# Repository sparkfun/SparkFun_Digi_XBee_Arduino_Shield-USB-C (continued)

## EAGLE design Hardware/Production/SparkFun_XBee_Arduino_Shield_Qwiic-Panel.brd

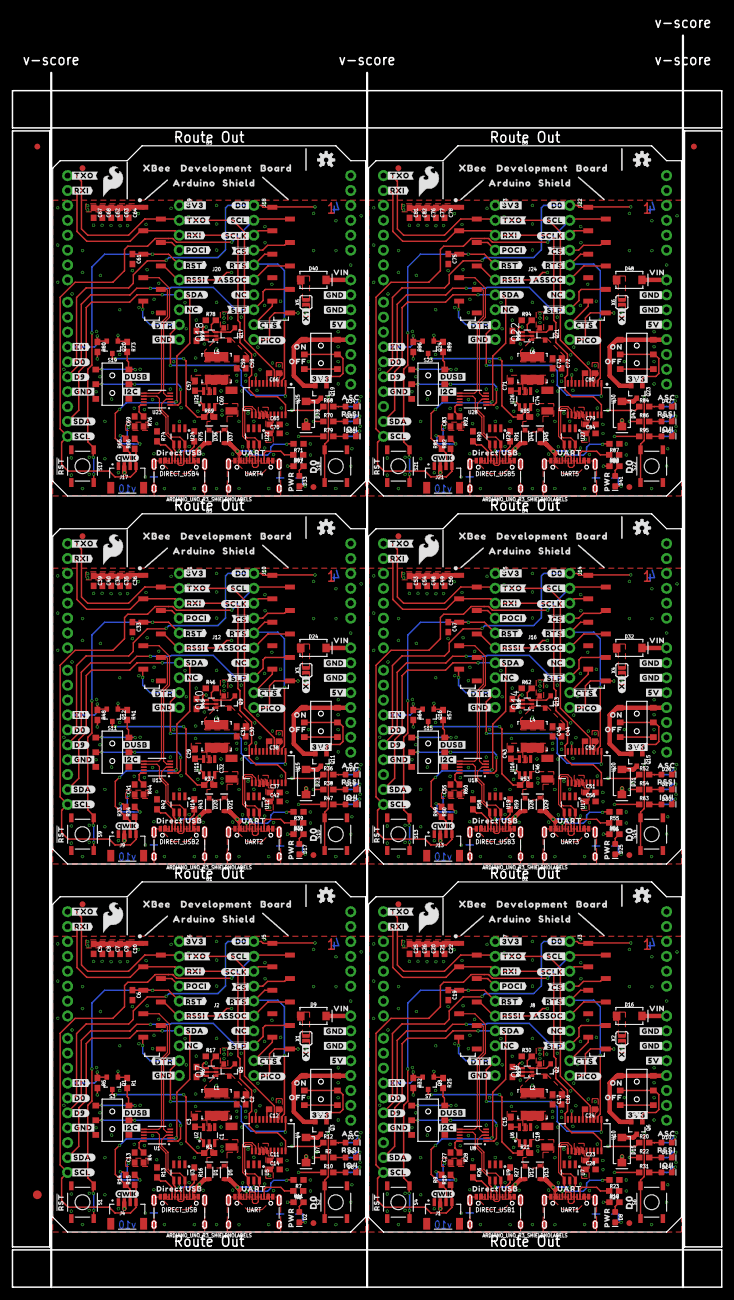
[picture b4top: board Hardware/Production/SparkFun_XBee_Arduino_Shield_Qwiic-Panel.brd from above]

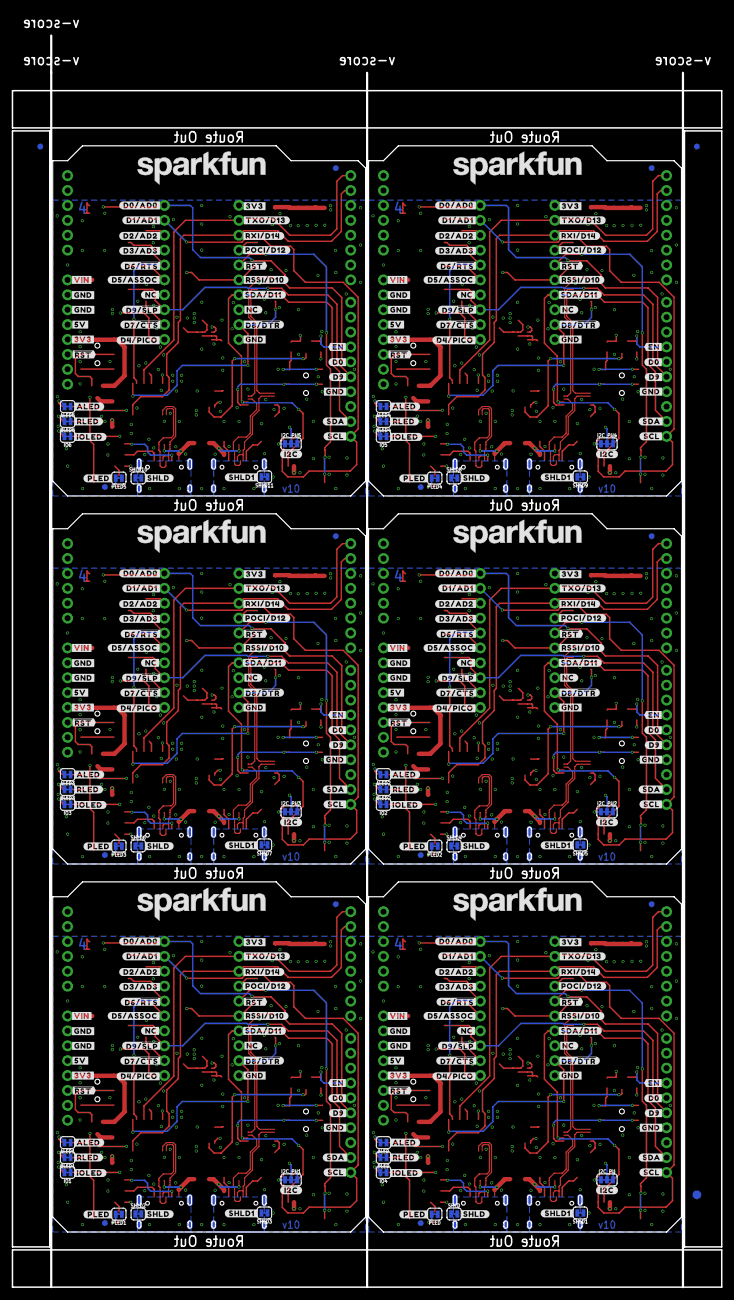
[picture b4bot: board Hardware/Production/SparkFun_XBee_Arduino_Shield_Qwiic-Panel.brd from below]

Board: 4 copper layers, 120.8 x 217.2 mm, 1008 parts (297 on the bottom side), 348 nets.

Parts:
ALED, ALED1, ALED2, ALED3, ALED4, ALED5: JUMPER-SMT_2_NC_TRACE_SILK; SMT-JUMPER_2_NC_TRACE_SILK
B1, B2, B3, B4, B5, B6: ARDUINO_UNO_R3_SHIELDNOLABELS; UNO_R3_SHIELD_NOLABELS
C1, C18, C32, C46, C60, C74: 10uF; 1210
C2, C4, C16, C17, C30, C31, C44, C45, C58, C59, C72, C73: 22uF; 0603
C3, C9, C11, C12, C13, C15, C21, C23, C24, C27, C29, C35, C37, C38, C41, C43, C49, C51, C52, C55, C57, C63, C65, C66, C69, C71, C77, C79, C80, C83: 0.1uF; 0603
C5, C25, C39, C53, C67, C81: 47pF; 0603
C6, C7, C19, C20, C33, C34, C47, C48, C61, C62, C75, C76: 10nF; 0603
C8, C26, C40, C54, C68, C82: 10pF; 0603
C10, C22, C36, C50, C64, C78: 10uF; 0603
C14, C28, C42, C56, C70, C84: 4.7uF; 0603
D1, D5, D12, D13, D20, D21, D28, D29, D36, D37, D44, D45: 3A/10V/280mV; SOD-323
D2, D8, D17, D25, D33, D41: RED; LED-0603
D3, D10, D18, D26, D34, D42: BLUE; LED-0603
D4, D11, D19, D27, D35, D43: Yellow; LED-0603
D6, D14, D22, D30, D38, D46: GREEN; LED-0603
D7, D9, D15, D16, D23, D24, D31, D32, D39, D40, D47, D48: 3A/40V/500mV; SMA-DIODE
DIRECT_USB, DIRECT_USB1, DIRECT_USB2, DIRECT_USB3, DIRECT_USB4, DIRECT_USB5: USB Female Type C Connector; USB-C-16P-4LAYER-ISOLATED
E$1, E$2, E$3, E$4: FIDUCIAL-1X2
E$5, E$6: FIDUCIAL-1.5X3
FD1, FD2, FD3, FD4, FD5, FD6, FD7, FD8, FD9, FD10, FD11, FD12, FD13, FD14, FD15, FD16, FD17, FD18, FD19, FD20, FD21, FD22, FD23, FD24: FIDUCIAL1X2; FIDUCIAL-1X2
I2C_PU, I2C_PU1, I2C_PU2, I2C_PU3, I2C_PU4, I2C_PU5: JUMPER-SMT_3_2-NC_TRACE_SILK; SMT-JUMPER_3_2-NC_TRACE_SILK
IO1, IO2, IO3, IO4, IO5, IO6: JUMPER-SMT_2_NC_TRACE_SILK; SMT-JUMPER_2_NC_TRACE_SILK
J1, J4, J9, J13, J17, J21: QWIIC_RIGHT_ANGLE; JST04_1MM_RA
J2, J8, J12, J16, J20, J24: XBEE3-SMD
J3, J5, J6, J7, J10, J11, J14, J15, J18, J19, J22, J23: 1X10_NO_SILK
L1, L2, L3, L4, L5, L6: 3.9UH; INDUCTOR_3.9UH
LOGO1, LOGO7, LOGO11, LOGO15, LOGO19, LOGO23: SFE_LOGO_NAMEBLANK; BLANK
LOGO2, LOGO5, LOGO9, LOGO13, LOGO17, LOGO21: OSHW-LOGOS; OSHW-LOGO-S
LOGO3, LOGO6, LOGO10, LOGO14, LOGO18, LOGO22: QWIIC_LOGO_4MM; QWIIC_4MM
LOGO4, LOGO8, LOGO12, LOGO16, LOGO20, LOGO24: SPECIAL_INSTRUCTIONS-ORDERING; ORDERING_INSTRUCTIONS
PLED, PLED1, PLED2, PLED3, PLED4, PLED5: JUMPER-SMT_2_NC_TRACE_SILK; SMT-JUMPER_2_NC_TRACE_SILK
Q1, Q8, Q12, Q16, Q20, Q24: 220mA/50V/3.5Ω; SOT23-3
Q2, Q5, Q9, Q13, Q17, Q21: 20V/4.2A/52mΩ/1.4W; SOT23-3
Q3, Q6, Q11, Q15, Q19, Q23: 3.1A/30V/105mΩ; SOT23-3
Q4, Q7, Q10, Q14, Q18, Q22: SOT363_PHILIPS
R1, R3, R6, R21, R25, R29, R37, R41, R45, R53, R57, R61, R69, R73, R77, R85, R89, R93: 100k; 0603
R2, R9, R12, R14, R15, R18, R20, R22, R33, R34, R36, R38, R49, R50, R52, R54, R65, R66, R68, R70, R81, R82, R84, R86: 2.2k; 0603
R4, R28, R44, R60, R76, R92: 100; 0603
R5, R32, R48, R64, R80, R96: 10k; 0603
R7, R8, R13, R16, R23, R24, R26, R27, R39, R40, R42, R43, R55, R56, R58, R59, R71, R72, R74, R75, R87, R88, R90, R91: 5.1k; 0603
R10, R31, R47, R63, R79, R95: 330; 0603
R11, R19, R35, R51, R67, R83: 4.7k; 0603
R17, R30, R46, R62, R78, R94: 1M; 0603
RLED, RLED1, RLED2, RLED3, RLED4, RLED5: JUMPER-SMT_2_NC_TRACE_SILK; SMT-JUMPER_2_NC_TRACE_SILK
S1, S2, S4, S6, S9, S10, S13, S14, S17, S18, S21, S22: TACTILE_SWITCH_SMD_5.2MM
S3, S5, S7, S8, S11, S12, S15, S16, S19, S20, S23, S24: SWITCH_DPDT_SMD_AYZ0202
SHLD, SHLD1, SHLD2, SHLD3, SHLD4, SHLD5, SHLD6, SHLD7, SHLD8, SHLD9, SHLD10, SHLD11: JUMPER-SMT_2_NC_TRACE_SILK; SMT-JUMPER_2_NC_TRACE_SILK
U1, U8, U13, U18, U23, U28: FSUSB30MUX_MSOP10; MSOP10
U2, U6, U11, U16, U21, U26: AP63203; SOT23-6
U3, U5, U7, U9, U12, U14, U17, U19, U22, U24, U27, U29: ESD Diode; SOT-23-6
U4, U10, U15, U20, U25, U30: FT231XS; SSOP20_L
U$1, U$146, U$238, U$330, U$422, U$514: RSSI31
U$2, U$147, U$239, U$331, U$423, U$515: PWR29
U$3, U$56, U$120, U$134, U$212, U$226, U$304, U$318, U$396, U$410, U$488, U$502: #SDA#10
U$4, U$127, U$219, U$311, U$403, U$495: #SHLD#36
U$5, U$9, U$128, U$133, U$220, U$225, U$312, U$317, U$404, U$409, U$496, U$501: #NC#1
U$6, U$99, U$191, U$283, U$375, U$467: #D3#AD3#23
U$7, U$10, U$129, U$130, U$221, U$222, U$313, U$314, U$405, U$406, U$497, U$498: #NC#3
U$8, U$159, U$251, U$343, U$435, U$527: ##DTR##27
U$11, U$97, U$189, U$281, U$373, U$465: #D1#AD1#8
U$12, U$160, U$252, U$344, U$436, U$528: ##CTS##28
U$13, U$105, U$197, U$289, U$381, U$473: #D8##DTR##27
U$14, U$106, U$198, U$290, U$382, U$474: #RSSI#D10#17
U$15, U$107, U$199, U$291, U$383, U$475: #SDA#D11#9
U$16, U$108, U$200, U$292, U$384, U$476: ##RST##15
U$17, U$109, U$201, U$293, U$385, U$477: #POCI#D12#24
U$18, U$110, U$202, U$294, U$386, U$478: #RXI#D14#15
U$19, U$98, U$190, U$282, U$374, U$466: #D2#AD2#19
U$20, U$100, U$192, U$284, U$376, U$468: #D6##RTS##25
U$21, U$32, U$115, U$137, U$207, U$229, U$299, U$321, U$391, U$413, U$483, U$505: #TXO#8
U$22, U$111, U$203, U$295, U$387, U$479: #TXO#D13#13
U$23, U$167, U$259, U$351, U$443, U$535: VIN5
U$24, U$135, U$227, U$319, U$411, U$503: #SCL#7
U$25, U$29, U$41, U$50, U$53, U$63, U$76, U$82, U$132, U$136, U$140, U$149, U$161, U$173, U$174, U$178, U$224, U$228, U$232, U$241, U$253, U$265, U$266, U$270, U$316, U$320, U$324, U$333, U$345, U$357, U$358, U$362, U$408, U$412, U$416, U$425, U$437, U$449, U$450, U$454, U$500, U$504, U$508, U$517, U$529, U$541, U$542, U$546: #GND#0
U$26, U$91, U$185, U$277, U$369, U$461: #I2C#33
U$27, U$33, U$116, U$138, U$208, U$230, U$300, U$322, U$392, U$414, U$484, U$506: #RXI#7
U$28, U$131, U$223, U$315, U$407, U$499: UART34
U$30, U$95, U$187, U$279, U$371, U$463: #RST#30
U$31, U$168, U$260, U$352, U$444, U$536: #PICO#27
U$34, U$169, U$261, U$353, U$445, U$537: #D9#6
U$35, U$101, U$193, U$285, U$377, U$469: #D5#ASSOC#25
U$36, U$102, U$194, U$286, U$378, U$470: #D9##SLP##28
U$37, U$103, U$195, U$287, U$379, U$471: #D7##CTS##26
U$38, U$104, U$196, U$288, U$380, U$472: #D4#PICO#25
U$39, U$66, U$155, U$175, U$247, U$267, U$339, U$359, U$431, U$451, U$523, U$543: #5V#5
U$40, U$92, U$186, U$278, U$370, U$462: D03
U$42, U$65, U$126, U$170, U$218, U$262, U$310, U$354, U$402, U$446, U$494, U$538: #D0#3
U$43, U$171, U$263, U$355, U$447, U$539: #X1#10
U$44, U$47, U$77, U$84, U$139, U$150, U$162, U$180, U$231, U$242, U$254, U$272, U$323, U$334, U$346, U$364, U$415, U$426, U$438, U$456, U$507, U$518, U$530, U$548: #3V3#1
U$45, U$117, U$209, U$301, U$393, U$485: #POCI#32
U$46, U$172, U$264, U$356, U$448, U$540: ON38
U$48, U$112, U$204, U$296, U$388, U$480: #EN#17
U$49, U$113, U$205, U$297, U$389, U$481: #ALED#21
U$51, U$114, U$206, U$298, U$390, U$482: #RLED#22
U$52, U$164, U$256, U$348, U$440, U$532: #PLED#20
U$54, U$87, U$118, U$181, U$210, U$273, U$302, U$365, U$394, U$457, U$486, U$549: ##RST##13
U$55, U$119, U$211, U$303, U$395, U$487: #RSSI#16
U$57, U$121, U$213, U$305, U$397, U$489: #ASSOC#28
U$58, U$122, U$214, U$306, U$398, U$490: ##RTS##14
U$59, U$123, U$215, U$307, U$399, U$491: ##CS##26
U$60, U$124, U$216, U$308, U$400, U$492: #SCLK#33
U$61, U$96, U$188, U$280, U$372, U$464: SFE_LOGO_FLAME_.2
U$62, U$141, U$233, U$325, U$417, U$509: SFE_LOGO_NAME_.2
U$64, U$125, U$217, U$309, U$401, U$493: #SCL#9
U$67, U$176, U$268, U$360, U$452, U$544: #SDA#9
U$68, U$142, U$234, U$326, U$418, U$510: ##SLP##28
U$69, U$163, U$255, U$347, U$439, U$531: OFF311
U$70, U$177, U$269, U$361, U$453, U$545: #SCL#13
U$71, U$143, U$235, U$327, U$419, U$511: DIRECT_USB33
U$72, U$144, U$236, U$328, U$420, U$512: #DUSB#31
U$73, U$158, U$250, U$342, U$434, U$526: #I2C#13751
U$74, U$145, U$237, U$329, U$421, U$513: ASC32
U$75, U$148, U$240, U$332, U$424, U$516: #SHLD1#37
U$78, U$151, U$243, U$335, U$427, U$519: #D0#AD0#18
U$79, U$152, U$244, U$336, U$428, U$520: ARDUINO1345
U$80, U$153, U$245, U$337, U$429, U$521: XBEE340
U$81, U$154, U$246, U$338, U$430, U$522: SHIELD1346
U$83, U$179, U$271, U$363, U$455, U$547: #EN#15
U$85, U$156, U$248, U$340, U$432, U$524: DEVELOPMENT1346
U$86, U$157, U$249, U$341, U$433, U$525: BOARD1347
U$88, U$182, U$274, U$366, U$458, U$550: #VIN#4
U$89, U$183, U$275, U$367, U$459, U$551: #D0#3416
U$90, U$184, U$276, U$368, U$460, U$552: #D9#3416
U$93, U$165, U$257, U$349, U$441, U$533: #IOLED#5
U$94, U$166, U$258, U$350, U$442, U$534: IO49
UART, UART1, UART2, UART3, UART4, UART5: USB Female Type C Connector; USB-C-16P-4LAYER-ISOLATED
X1, X2, X3, X4, X5, X6: JUMPER-SMT_2_NO_SILK; SMT-JUMPER_2_NO_SILK

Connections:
3.3V: C5.1, C7.1, C8.1, C9.1, C10.1, C11.1, C12.1, C13.1, C14.1, D7.C, I2C_PU.2, J2.1, J4.2, J6.1, Q1.1, Q5.2, Q7.4, R1.1, R4.2, R5.2, R11.1, U4.3, U4.13, U4.14, U4.15
3.3V1: C20.1, C21.1, C22.1, C23.1, C24.1, C25.1, C26.1, C27.1, C28.1, D15.C, I2C_PU1.2, J1.2, J7.1, J8.1, Q2.2, Q4.4, Q8.1, R19.1, R25.1, R28.2, R32.2, U10.3, U10.13, U10.14, U10.15
3.3V2: C34.1, C35.1, C36.1, C37.1, C38.1, C39.1, C40.1, C41.1, C42.1, D23.C, I2C_PU2.2, J9.2, J11.1, J12.1, Q9.2, Q10.4, Q12.1, R35.1, R41.1, R44.2, R48.2, U15.3, U15.13, U15.14, U15.15
3.3V3: C48.1, C49.1, C50.1, C51.1, C52.1, C53.1, C54.1, C55.1, C56.1, D31.C, I2C_PU3.2, J13.2, J15.1, J16.1, Q13.2, Q14.4, Q16.1, R51.1, R57.1, R60.2, R64.2, U20.3, U20.13, U20.14, U20.15
3.3V4: C62.1, C63.1, C64.1, C65.1, C66.1, C67.1, C68.1, C69.1, C70.1, D39.C, I2C_PU4.2, J17.2, J19.1, J20.1, Q17.2, Q18.4, Q20.1, R67.1, R73.1, R76.2, R80.2, U25.3, U25.13, U25.14, U25.15
3.3V5: C76.1, C77.1, C78.1, C79.1, C80.1, C81.1, C82.1, C83.1, C84.1, D47.C, I2C_PU5.2, J21.2, J23.1, J24.1, Q21.2, Q22.4, Q24.1, R83.1, R89.1, R92.2, R96.2, U30.3, U30.13, U30.14, U30.15
3.3V_SW: B1.3.3V, Q3.2, S5.3, S5.6
3.3V_SW1: B2.3.3V, Q6.2, S8.3, S8.6
3.3V_SW2: B3.3.3V, Q11.2, S12.3, S12.6
3.3V_SW3: B4.3.3V, Q15.2, S16.3, S16.6
3.3V_SW4: B5.3.3V, Q19.2, S20.3, S20.6
3.3V_SW5: B6.3.3V, Q23.2, S24.3, S24.6
3.3V_VREG: C2.1, C4.1, L1.P$2, Q5.3, Q7.1, U2.1
3.3V_VREG1: C16.1, C17.1, L2.P$2, Q2.3, Q4.1, U6.1
3.3V_VREG2: C30.1, C31.1, L3.P$2, Q9.3, Q10.1, U11.1
3.3V_VREG3: C44.1, C45.1, L4.P$2, Q13.3, Q14.1, U16.1
3.3V_VREG4: C58.1, C59.1, L5.P$2, Q17.3, Q18.1, U21.1
3.3V_VREG5: C72.1, C73.1, L6.P$2, Q21.3, Q22.1, U26.1
!RESET!: C6.1, J2.5, J6.5, S1.1, S1.2
!RESET!1: C19.1, J7.5, J8.5, S4.1, S4.2
!RESET!2: C33.1, J11.5, J12.5, S9.1, S9.2
!RESET!3: C47.1, J15.5, J16.5, S13.1, S13.2
!RESET!4: C61.1, J19.5, J20.5, S17.1, S17.2
!RESET!5: C75.1, J23.5, J24.5, S21.1, S21.2
D0: B1.D12, J2.20, J5.1, S2.1, S2.2
D1: B2.D12, J3.1, J8.20, S6.1, S6.2
D1/SCL: B1.SCL, J2.19, J4.4, J5.2, R15.1
D1/SCL1: B2.SCL, J1.4, J3.2, J8.19, R18.1
D1/SCL2: B3.SCL, J9.4, J10.2, J12.19, R34.1
D1/SCL3: B4.SCL, J13.4, J14.2, J16.19, R50.1
D1/SCL4: B5.SCL, J17.4, J18.2, J20.19, R66.1
D1/SCL5: B6.SCL, J21.4, J22.2, J24.19, R82.1
D2: B3.D12, J10.1, J12.20, S10.1, S10.2
D2/SPI_CLK: J2.18, J5.3
D2/SPI_CLK1: J3.3, J8.18
D2/SPI_CLK2: J10.3, J12.18
D2/SPI_CLK3: J14.3, J16.18
D2/SPI_CLK4: J18.3, J20.18
D2/SPI_CLK5: J22.3, J24.18
D3: B4.D12, J14.1, J16.20, S14.1, S14.2
D3/SPI_!CS!: J2.17, J5.4
D3/SPI_!CS!1: J3.4, J8.17
D3/SPI_!CS!2: J10.4, J12.17
D3/SPI_!CS!3: J14.4, J16.17
D3/SPI_!CS!4: J18.4, J20.17
D3/SPI_!CS!5: J22.4, J24.17
D4: B5.D12, J18.1, J20.20, S18.1, S18.2
D4/SPI_PICO: J2.11, J5.10, R10.1
D4/SPI_PICO1: J3.10, J8.11, R31.1
D4/SPI_PICO2: J10.10, J12.11, R47.1
D4/SPI_PICO3: J14.10, J16.11, R63.1
D4/SPI_PICO4: J18.10, J20.11, R79.1
D4/SPI_PICO5: J22.10, J24.11, R95.1
D5: B6.D12, J22.1, J24.20, S22.1, S22.2
D5/ASSOCIATE: J2.15, J5.6, R12.1
D5/ASSOCIATE1: J3.6, J8.15, R20.1
D5/ASSOCIATE2: J10.6, J12.15, R36.1
D5/ASSOCIATE3: J14.6, J16.15, R52.1
D5/ASSOCIATE4: J18.6, J20.15, R68.1
D5/ASSOCIATE5: J22.6, J24.15, R84.1
D6/!RTS!: J2.16, J5.5, U4.2
D6/!RTS!1: J3.5, J8.16, U10.2
D6/!RTS!2: J10.5, J12.16, U15.2
D6/!RTS!3: J14.5, J16.16, U20.2
D6/!RTS!4: J18.5, J20.16, U25.2
D6/!RTS!5: J22.5, J24.16, U30.2
D7/!CTS!: J2.12, J5.9, U4.9
D7/!CTS!1: J3.9, J8.12, U10.9
D7/!CTS!2: J10.9, J12.12, U15.9
D7/!CTS!3: J14.9, J16.12, U20.9
D7/!CTS!4: J18.9, J20.12, U25.9
D7/!CTS!5: J22.9, J24.12, U30.9
D8/!DTR!: J2.9, J6.9, U4.1
D8/!DTR!1: J7.9, J8.9, U10.1
D8/!DTR!2: J11.9, J12.9, U15.1
D8/!DTR!3: J15.9, J16.9, U20.1
D8/!DTR!4: J19.9, J20.9, U25.1
D8/!DTR!5: J23.9, J24.9, U30.1
D9/!SLEEP!: B1.D13, J2.13, J5.8
D9/!SLEEP!1: B2.D13, J3.8, J8.13
D9/!SLEEP!2: B3.D13, J10.8, J12.13
D9/!SLEEP!3: B4.D13, J14.8, J16.13
D9/!SLEEP!4: B5.D13, J18.8, J20.13
D9/!SLEEP!5: B6.D13, J22.8, J24.13
D10/RSSI_PWM: J2.6, J6.6, R2.1
D10/RSSI_PWM1: J7.6, J8.6, R22.1
D10/RSSI_PWM2: J11.6, J12.6, R38.1
D10/RSSI_PWM3: J15.6, J16.6, R54.1
D10/RSSI_PWM4: J19.6, J20.6, R70.1
D10/RSSI_PWM5: J23.6, J24.6, R86.1
D11/SDA: B1.SDA, J4.3, J6.7, R14.1, U1.2
D11/SDA1: B2.SDA, J1.3, J7.7, R9.1, U8.2
D11/SDA2: B3.SDA, J9.3, J11.7, R33.1, U13.2
D11/SDA3: B4.SDA, J13.3, J15.7, R49.1, U18.2
D11/SDA4: B5.SDA, J17.3, J19.7, R65.1, U23.2
D11/SDA5: B6.SDA, J21.3, J23.7, R81.1, U28.2
D12/SPI_POCI: J2.4, J6.4
D12/SPI_POCI1: J7.4, J8.4
D12/SPI_POCI2: J11.4, J12.4
D12/SPI_POCI3: J15.4, J16.4
D12/SPI_POCI4: J19.4, J20.4
D12/SPI_POCI5: J23.4, J24.4
D13/TXO: B1.RX, J2.2, J6.2, U4.4
D13/TXO1: B2.RX, J7.2, J8.2, U10.4
D13/TXO2: B3.RX, J11.2, J12.2, U15.4
D13/TXO3: B4.RX, J15.2, J16.2, U20.4
D13/TXO4: B5.RX, J19.2, J20.2, U25.4
D13/TXO5: B6.RX, J23.2, J24.2, U30.4
D14/RXI: B1.TX, J2.3, J6.3, U4.20
D14/RXI1: B2.TX, J7.3, J8.3, U10.20
D14/RXI2: B3.TX, J11.3, J12.3, U15.20
D14/RXI3: B4.TX, J15.3, J16.3, U20.20
D14/RXI4: B5.TX, J19.3, J20.3, U25.20
D14/RXI5: B6.TX, J23.3, J24.3, U30.20
D+: U4.11, U5.6, UART.A6, UART.B6
D+1: U7.6, U10.11, UART1.A6, UART1.B6
D+2: U12.6, U15.11, UART2.A6, UART2.B6
D+3: U17.6, U20.11, UART3.A6, UART3.B6
D+4: U22.6, U25.11, UART4.A6, UART4.B6
D+5: U27.6, U30.11, UART5.A6, UART5.B6
D-: U4.12, U5.4, UART.A7, UART.B7
D-1: U7.4, U10.12, UART1.A7, UART1.B7
D-2: U12.4, U15.12, UART2.A7, UART2.B7
D-3: U17.4, U20.12, UART3.A7, UART3.B7
D-4: U22.4, U25.12, UART4.A7, UART4.B7
D-5: U27.4, U30.12, UART5.A7, UART5.B7
DIRECT_D+: DIRECT_USB.A6, DIRECT_USB.B6, U1.3, U3.6
DIRECT_D+1: DIRECT_USB1.A6, DIRECT_USB1.B6, U8.3, U9.6
DIRECT_D+2: DIRECT_USB2.A6, DIRECT_USB2.B6, U13.3, U14.6
DIRECT_D+3: DIRECT_USB3.A6, DIRECT_USB3.B6, U18.3, U19.6
DIRECT_D+4: DIRECT_USB4.A6, DIRECT_USB4.B6, U23.3, U24.6
DIRECT_D+5: DIRECT_USB5.A6, DIRECT_USB5.B6, U28.3, U29.6
DIRECT_D-: DIRECT_USB.A7, DIRECT_USB.B7, U1.7, U3.4
DIRECT_D-1: DIRECT_USB1.A7, DIRECT_USB1.B7, U8.7, U9.4
DIRECT_D-2: DIRECT_USB2.A7, DIRECT_USB2.B7, U13.7, U14.4
DIRECT_D-3: DIRECT_USB3.A7, DIRECT_USB3.B7, U18.7, U19.4
DIRECT_D-4: DIRECT_USB4.A7, DIRECT_USB4.B7, U23.7, U24.4
DIRECT_D-5: DIRECT_USB5.A7, DIRECT_USB5.B7, U28.7, U29.4
DIRECT_SELECT: S3.2, S3.5, U1.1
DIRECT_SELECT1: S7.2, S7.5, U8.1
DIRECT_SELECT2: S11.2, S11.5, U13.1
DIRECT_SELECT3: S15.2, S15.5, U18.1
DIRECT_SELECT4: S19.2, S19.5, U23.1
DIRECT_SELECT5: S23.2, S23.5, U28.1
DIRECT_USB: R1.2, S3.1, S3.4
DIRECT_USB1: R25.2, S7.1, S7.4
DIRECT_USB2: R41.2, S11.1, S11.4
DIRECT_USB3: R57.2, S15.1, S15.4
DIRECT_USB4: R73.2, S19.1, S19.4
DIRECT_USB5: R89.2, S23.1, S23.4
EN: Q1.3, R3.1, U2.2
EN1: Q8.3, R21.1, U6.2
EN2: Q12.3, R37.1, U11.2
EN3: Q16.3, R53.1, U16.2
EN4: Q20.3, R69.1, U21.2
EN5: Q24.3, R85.1, U26.2
EN-TRANS: B1.D11, Q1.2, R5.1
EN-TRANS1: B2.D11, Q8.2, R32.1
EN-TRANS2: B3.D11, Q12.2, R48.1
EN-TRANS3: B4.D11, Q16.2, R64.1
EN-TRANS4: B5.D11, Q20.2, R80.1
EN-TRANS5: B6.D11, Q24.2, R96.1
GND: ALED.1, B1.GND@0, B1.GND@1, B1.GND@2, C1.2, C2.2, C4.2, C5.2, C6.2, C7.2, C8.2, C9.2, C10.2, C11.2, C12.2, C13.2, C14.2, DIRECT_USB.GND, DIRECT_USB.GND2, IO4.1, J2.10, J4.1, J6.10, PLED.1, R6.1, R7.1, R8.1, R13.1, R16.1, R17.1, RLED.1, S1.3, S1.4, S2.3, S2.4, S3.3, S3.6, S5.1, S5.4, SHLD.1, SHLD1.1, U1.5, U1.9, U2.4, U3.2, U4.6, U4.16, U5.2, UART.GND, UART.GND2
GND1: ALED1.1, B2.GND@0, B2.GND@1, B2.GND@2, C16.2, C17.2, C18.2, C19.2, C20.2, C21.2, C22.2, C23.2, C24.2, C25.2, C26.2, C27.2, C28.2, DIRECT_USB1.GND, DIRECT_USB1.GND2, IO1.1, J1.1, J7.10, J8.10, PLED1.1, R23.1, R24.1, R26.1, R27.1, R29.1, R30.1, RLED1.1, S4.3, S4.4, S6.3, S6.4, S7.3, S7.6, S8.1, S8.4, SHLD2.1, SHLD3.1, U6.4, U7.2, U8.5, U8.9, U9.2, U10.6, U10.16, UART1.GND, UART1.GND2
GND2: ALED2.1, B3.GND@0, B3.GND@1, B3.GND@2, C30.2, C31.2, C32.2, C33.2, C34.2, C35.2, C36.2, C37.2, C38.2, C39.2, C40.2, C41.2, C42.2, DIRECT_USB2.GND, DIRECT_USB2.GND2, IO2.1, J9.1, J11.10, J12.10, PLED2.1, R39.1, R40.1, R42.1, R43.1, R45.1, R46.1, RLED2.1, S9.3, S9.4, S10.3, S10.4, S11.3, S11.6, S12.1, S12.4, SHLD4.1, SHLD5.1, U11.4, U12.2, U13.5, U13.9, U14.2, U15.6, U15.16, UART2.GND, UART2.GND2
GND3: ALED3.1, B4.GND@0, B4.GND@1, B4.GND@2, C44.2, C45.2, C46.2, C47.2, C48.2, C49.2, C50.2, C51.2, C52.2, C53.2, C54.2, C55.2, C56.2, DIRECT_USB3.GND, DIRECT_USB3.GND2, IO3.1, J13.1, J15.10, J16.10, PLED3.1, R55.1, R56.1, R58.1, R59.1, R61.1, R62.1, RLED3.1, S13.3, S13.4, S14.3, S14.4, S15.3, S15.6, S16.1, S16.4, SHLD6.1, SHLD7.1, U16.4, U17.2, U18.5, U18.9, U19.2, U20.6, U20.16, UART3.GND, UART3.GND2
GND4: ALED4.1, B5.GND@0, B5.GND@1, B5.GND@2, C58.2, C59.2, C60.2, C61.2, C62.2, C63.2, C64.2, C65.2, C66.2, C67.2, C68.2, C69.2, C70.2, DIRECT_USB4.GND, DIRECT_USB4.GND2, IO5.1, J17.1, J19.10, J20.10, PLED4.1, R71.1, R72.1, R74.1, R75.1, R77.1, R78.1, RLED4.1, S17.3, S17.4, S18.3, S18.4, S19.3, S19.6, S20.1, S20.4, SHLD8.1, SHLD9.1, U21.4, U22.2, U23.5, U23.9, U24.2, U25.6, U25.16, UART4.GND, UART4.GND2
GND5: ALED5.1, B6.GND@0, B6.GND@1, B6.GND@2, C72.2, C73.2, C74.2, C75.2, C76.2, C77.2, C78.2, C79.2, C80.2, C81.2, C82.2, C83.2, C84.2, DIRECT_USB5.GND, DIRECT_USB5.GND2, IO6.1, J21.1, J23.10, J24.10, PLED5.1, R87.1, R88.1, R90.1, R91.1, R93.1, R94.1, RLED5.1, S21.3, S21.4, S22.3, S22.4, S23.3, S23.6, S24.1, S24.4, SHLD10.1, SHLD11.1, U26.4, U27.2, U28.5, U28.9, U29.2, U30.6, U30.16, UART5.GND, UART5.GND2
unnamed: C3.1, U2.6
unnamed: D4.A, R2.2
unnamed: D4.C, RLED.2
unnamed: D6.A, R10.2
unnamed: R8.2, UART.B5
unnamed: R7.2, UART.A5
unnamed: D2.A, R11.2
unnamed: C3.2, L1.P$1, U2.5
unnamed: D9.A, X1.2
unnamed: R4.1, U1.10
unnamed: I2C_PU.3, R14.2
unnamed: D3.A, R12.2
unnamed: I2C_PU.1, R15.2
unnamed: DIRECT_USB.B5, R16.2
unnamed: DIRECT_USB.A5, R13.2
unnamed: D7.A, Q3.3
unnamed: D6.C, IO4.2
unnamed: I2C_PU1.3, R9.2
unnamed: Q7.2, Q7.5, Q7.6, R6.2
unnamed: Q5.1, Q7.3, R17.2
unnamed: ALED.2, D3.C
unnamed: I2C_PU1.1, R18.2
unnamed: D2.C, PLED.2
unnamed: D8.A, R19.2
unnamed: D10.A, R20.2
unnamed: ALED1.2, D10.C
unnamed: Q3.1, S5.2, S5.5
unnamed: D8.C, PLED1.2
unnamed: C15.1, U6.6
unnamed: C15.2, L2.P$1, U6.5
unnamed: D11.A, R22.2
unnamed: D11.C, RLED1.2
unnamed: R24.2, UART1.B5
unnamed: R23.2, UART1.A5
unnamed: DIRECT_USB1.B5, R27.2
unnamed: DIRECT_USB1.A5, R26.2
unnamed: R28.1, U8.10
unnamed: Q4.2, Q4.5, Q4.6, R29.2
unnamed: Q2.1, Q4.3, R30.2
unnamed: D14.A, R31.2
unnamed: D14.C, IO1.2
unnamed: Q6.1, S8.2, S8.5
unnamed: D15.A, Q6.3
unnamed: D16.A, X2.2
unnamed: I2C_PU2.3, R33.2
unnamed: I2C_PU2.1, R34.2
unnamed: D17.A, R35.2
unnamed: D18.A, R36.2
unnamed: ALED2.2, D18.C
unnamed: D17.C, PLED2.2
unnamed: C29.1, U11.6
unnamed: C29.2, L3.P$1, U11.5
unnamed: D19.A, R38.2
unnamed: D19.C, RLED2.2
unnamed: R40.2, UART2.B5
unnamed: R39.2, UART2.A5
unnamed: DIRECT_USB2.B5, R43.2
unnamed: DIRECT_USB2.A5, R42.2
unnamed: R44.1, U13.10
unnamed: Q10.2, Q10.5, Q10.6, R45.2
unnamed: Q9.1, Q10.3, R46.2
unnamed: D22.A, R47.2
unnamed: D22.C, IO2.2
unnamed: Q11.1, S12.2, S12.5
unnamed: D23.A, Q11.3
unnamed: D24.A, X3.2
unnamed: I2C_PU3.3, R49.2
unnamed: I2C_PU3.1, R50.2
unnamed: D25.A, R51.2
unnamed: D26.A, R52.2
unnamed: ALED3.2, D26.C
unnamed: D25.C, PLED3.2
unnamed: C43.1, U16.6
unnamed: C43.2, L4.P$1, U16.5
unnamed: D27.A, R54.2
unnamed: D27.C, RLED3.2
unnamed: R56.2, UART3.B5
unnamed: R55.2, UART3.A5
unnamed: DIRECT_USB3.B5, R59.2
unnamed: DIRECT_USB3.A5, R58.2
unnamed: R60.1, U18.10
unnamed: Q14.2, Q14.5, Q14.6, R61.2
unnamed: Q13.1, Q14.3, R62.2
unnamed: D30.A, R63.2
unnamed: D30.C, IO3.2
unnamed: Q15.1, S16.2, S16.5
unnamed: D31.A, Q15.3
unnamed: D32.A, X4.2
unnamed: I2C_PU4.3, R65.2
unnamed: I2C_PU4.1, R66.2
unnamed: D33.A, R67.2
unnamed: D34.A, R68.2
unnamed: ALED4.2, D34.C
unnamed: D33.C, PLED4.2
unnamed: C57.1, U21.6
unnamed: C57.2, L5.P$1, U21.5
unnamed: D35.A, R70.2
unnamed: D35.C, RLED4.2
unnamed: R72.2, UART4.B5
unnamed: R71.2, UART4.A5
unnamed: DIRECT_USB4.B5, R75.2
unnamed: DIRECT_USB4.A5, R74.2
unnamed: R76.1, U23.10
unnamed: Q18.2, Q18.5, Q18.6, R77.2
unnamed: Q17.1, Q18.3, R78.2
unnamed: D38.A, R79.2
unnamed: D38.C, IO5.2
unnamed: Q19.1, S20.2, S20.5
unnamed: D39.A, Q19.3
unnamed: D40.A, X5.2
unnamed: I2C_PU5.3, R81.2
unnamed: I2C_PU5.1, R82.2
unnamed: D41.A, R83.2
unnamed: D42.A, R84.2
unnamed: ALED5.2, D42.C
unnamed: D41.C, PLED5.2
unnamed: C71.1, U26.6
unnamed: C71.2, L6.P$1, U26.5
unnamed: D43.A, R86.2
unnamed: D43.C, RLED5.2
unnamed: R88.2, UART5.B5
unnamed: R87.2, UART5.A5
unnamed: DIRECT_USB5.B5, R91.2
unnamed: DIRECT_USB5.A5, R90.2
unnamed: R92.1, U28.10
unnamed: Q22.2, Q22.5, Q22.6, R93.2
unnamed: Q21.1, Q22.3, R94.2
unnamed: D46.A, R95.2
unnamed: D46.C, IO6.2
unnamed: Q23.1, S24.2, S24.5
unnamed: D47.A, Q23.3
unnamed: D48.A, X6.2
SHLD: SHLD.2, UART.SHLD1, UART.SHLD2, UART.SHLD3, UART.SHLD4, UART.SHLD5, UART.SHLD6, UART.SHLD7, UART.SHLD8
SHLD1: DIRECT_USB.SHLD1, DIRECT_USB.SHLD2, DIRECT_USB.SHLD3, DIRECT_USB.SHLD4, DIRECT_USB.SHLD5, DIRECT_USB.SHLD6, DIRECT_USB.SHLD7, DIRECT_USB.SHLD8, SHLD1.2
SHLD2: SHLD2.2, UART1.SHLD1, UART1.SHLD2, UART1.SHLD3, UART1.SHLD4, UART1.SHLD5, UART1.SHLD6, UART1.SHLD7, UART1.SHLD8
SHLD3: DIRECT_USB1.SHLD1, DIRECT_USB1.SHLD2, DIRECT_USB1.SHLD3, DIRECT_USB1.SHLD4, DIRECT_USB1.SHLD5, DIRECT_USB1.SHLD6, DIRECT_USB1.SHLD7, DIRECT_USB1.SHLD8, SHLD3.2
SHLD4: SHLD4.2, UART2.SHLD1, UART2.SHLD2, UART2.SHLD3, UART2.SHLD4, UART2.SHLD5, UART2.SHLD6, UART2.SHLD7, UART2.SHLD8
SHLD5: DIRECT_USB2.SHLD1, DIRECT_USB2.SHLD2, DIRECT_USB2.SHLD3, DIRECT_USB2.SHLD4, DIRECT_USB2.SHLD5, DIRECT_USB2.SHLD6, DIRECT_USB2.SHLD7, DIRECT_USB2.SHLD8, SHLD5.2
SHLD6: SHLD6.2, UART3.SHLD1, UART3.SHLD2, UART3.SHLD3, UART3.SHLD4, UART3.SHLD5, UART3.SHLD6, UART3.SHLD7, UART3.SHLD8
SHLD7: DIRECT_USB3.SHLD1, DIRECT_USB3.SHLD2, DIRECT_USB3.SHLD3, DIRECT_USB3.SHLD4, DIRECT_USB3.SHLD5, DIRECT_USB3.SHLD6, DIRECT_USB3.SHLD7, DIRECT_USB3.SHLD8, SHLD7.2
SHLD8: SHLD8.2, UART4.SHLD1, UART4.SHLD2, UART4.SHLD3, UART4.SHLD4, UART4.SHLD5, UART4.SHLD6, UART4.SHLD7, UART4.SHLD8
SHLD9: DIRECT_USB4.SHLD1, DIRECT_USB4.SHLD2, DIRECT_USB4.SHLD3, DIRECT_USB4.SHLD4, DIRECT_USB4.SHLD5, DIRECT_USB4.SHLD6, DIRECT_USB4.SHLD7, DIRECT_USB4.SHLD8, SHLD9.2
SHLD10: SHLD10.2, UART5.SHLD1, UART5.SHLD2, UART5.SHLD3, UART5.SHLD4, UART5.SHLD5, UART5.SHLD6, UART5.SHLD7, UART5.SHLD8
SHLD11: DIRECT_USB5.SHLD1, DIRECT_USB5.SHLD2, DIRECT_USB5.SHLD3, DIRECT_USB5.SHLD4, DIRECT_USB5.SHLD5, DIRECT_USB5.SHLD6, DIRECT_USB5.SHLD7, DIRECT_USB5.SHLD8, SHLD11.2
VCC: C1.1, D1.C, D5.C, R3.2, U2.3, X1.1
VCC1: C18.1, D12.C, D13.C, R21.2, U6.3, X2.1
VCC2: C32.1, D20.C, D21.C, R37.2, U11.3, X3.1
VCC3: C46.1, D28.C, D29.C, R53.2, U16.3, X4.1
VCC4: C60.1, D36.C, D37.C, R69.2, U21.3, X5.1
VCC5: C74.1, D44.C, D45.C, R85.2, U26.3, X6.1
VIN: B1.VIN, D9.C
VIN1: B2.VIN, D16.C
VIN2: B3.VIN, D24.C
VIN3: B4.VIN, D32.C
VIN4: B5.VIN, D40.C
VIN5: B6.VIN, D48.C
V_USB: D5.A, U5.5, UART.VBUS1, UART.VBUS2
V_USB1: D13.A, U7.5, UART1.VBUS1, UART1.VBUS2
V_USB2: D21.A, U12.5, UART2.VBUS1, UART2.VBUS2
V_USB3: D29.A, U17.5, UART3.VBUS1, UART3.VBUS2
V_USB4: D37.A, U22.5, UART4.VBUS1, UART4.VBUS2
V_USB5: D45.A, U27.5, UART5.VBUS1, UART5.VBUS2
V_USB_1: D12.A, DIRECT_USB1.VBUS1, DIRECT_USB1.VBUS2, U9.5
V_USB_2: D1.A, DIRECT_USB.VBUS1, DIRECT_USB.VBUS2, U3.5
V_USB_3: D20.A, DIRECT_USB2.VBUS1, DIRECT_USB2.VBUS2, U14.5
V_USB_4: D28.A, DIRECT_USB3.VBUS1, DIRECT_USB3.VBUS2, U19.5
V_USB_5: D36.A, DIRECT_USB4.VBUS1, DIRECT_USB4.VBUS2, U24.5
V_USB_6: D44.A, DIRECT_USB5.VBUS1, DIRECT_USB5.VBUS2, U29.5
XBEE_D+/SDA: J2.7, U1.4
XBEE_D+/SDA1: J8.7, U8.4
XBEE_D+/SDA2: J12.7, U13.4
XBEE_D+/SDA3: J16.7, U18.4
XBEE_D+/SDA4: J20.7, U23.4
XBEE_D+/SDA5: J24.7, U28.4
XBEE_D-: J2.8, U1.6
XBEE_D-1: J8.8, U8.6
XBEE_D-2: J12.8, U13.6
XBEE_D-3: J16.8, U18.6
XBEE_D-4: J20.8, U23.6
XBEE_D-5: J24.8, U28.6

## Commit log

2023-02-07 General placement of parts
2023-02-07 More changes to part placement
2023-02-08 Rearranges USB-C and Qwiic connectors
2023-02-08 Routes some nets ( feels good now )
2023-02-08 Routes more stuff
2023-02-08 Routes stuff in a sloppy manner - getting rid of airwires
2023-02-08 Routes air wires
2023-02-09 Improves routing spaghetti
2023-02-09 Updates many traces
2023-02-09 Makes all drill sizes uniform (0.012")
2023-02-09 Adds some silk
2023-03-06 Adds FT231XS, pushes all signals to bottom layer that were on layer two
    * Adds decoupling cap and 100 Ohm resistor to UART MUX
    * Moves some silk around
2023-03-06 More vias, improves routing
2023-03-06 Renames board files
2023-03-09 Routes all airwires, adds most silk labels
2023-03-13 Adds all silk
2023-03-13 Adds Measures
2023-03-13 Puts the measures in the previous commit onto the measures layers
2023-03-14 Arduino shield now with more level translators!
2023-03-14 Adds silk in relevant places
2023-03-14 Adds more stitching vias and silk labels
2023-03-15 Adds decoupling caps to TXS0108E and attempts to fix the silk
2023-03-15 Adds a few more labels
2023-03-16 Fixes a number of silk issues
    * Decreases the length delta (haha) between Direct USB data lines
    * Adds some clarifying text to the USB connectors
    * Adds title to the USB Mux section
    * Adjusts a number of traces around for better ground pour
    * Moves resistors away from LEDs so that the parts are not so cramped
2023-03-16 Fixes new wire stub DRC issues,
2023-03-16 Adds "1, 2, 3, 4" to layers and special ordering instructions
2023-03-16 Fixes wire stub DRC error
2023-03-16 Adjusts two silk labels ever so slightly
2023-03-16 Adds protos
2023-03-16 Renames proto zip file to include version
2023-04-06 Rolls to v02
    * Fixes USB data lines on main UART
    * Shifts ASC, RSSI nets to LEDs to be non-translated by default
    * Move SCL data line to non-translated by default
2023-04-27 Adds new power control circuits
2023-04-27 Routes most of the new air wires
2023-05-01 Improvements to power selection
    * Routes airwires
    * Fixes some silk
2023-05-01 Adds silk
    * Adds enable net, needs route
2023-05-02 Routes enable pin
2023-05-03 Replaces the PCHAN with a more suitable one
    * Routing improvements
2023-05-03 Adds silk
2023-05-03 Adds 10k between source and gate on PCHAN circuit
    * Switches two resistor values to 0402 so that everything can fit.
2023-05-03 Adds more vias
    * Improves routing
2023-05-04 Adds diode to high side switch, adds note to 10k resistor
    * Removes voltage divider between NCHAN mosfet and the gates of the PCHAN mosfets
2023-05-18 Adds new switch
2023-05-18 Adds some rough drafts
2023-05-18 v03 changes
    * Replaces bi-directional power switch with jumper
    * Removes level translators
    * Removes a majority of nets connecting to R3 PTH
2023-05-18 Optimizes traces
2023-05-19 Improves spacing in schematic
    * Improves ground pour
2023-05-19 Adds silk and vias
2023-05-19 Adds more vias!!
2023-05-19 Adds more measures and additional notes in the schematic
2023-05-19 Adds more measures, vias, and notes
    * Rolls version to v10
2023-05-19 Adds production panel, fixes acid trap
2023-05-24 Adds Gerbers, updates ordering instructions to include material
    * Fixes "Off" and "On" silk on switch
2023-05-24 Replaces old USB mux switch with new one
    * Removes 100Ohm resistor on VCC line
2023-05-24 Small adjustment to design file after approving proximity DRC error
    * Remakes panels
    * Deletes old library
2023-07-10 Adds switch to UART lines for disconnect
2023-07-14 Changes silk on switch and increments the version number
2023-07-14 Adds new v11 panel
2023-07-14 Removes old zip files and renames the new ones
2023-08-01 Initial checkin of docs
2023-09-12 Periodic check in
2023-09-18 Removes UART and direction communication
2023-09-20 Moves USB-C to center of board
2023-09-20 Reroutes switch
2023-10-09 Adds jumpers for alternate serial pins, removes some text from schematic, moves power LED closer to USB-C
2023-10-09 Cleans up some more schematic elements
2023-10-10 Reconnects I2c lines, deletes old nets, removes diode from VUSB to VCC
2023-10-12 Power fixes
    * Adds power isolation translation on I2C data lines using NCHAN mosfets
    * Moves the pullup on the VREG "EN" pin to use R3/R4 power rail - "3v3_SW"
    * Adds 100k to drain of PCHAN mosfet that sits between the 3v3 rail of R3/R4 line and 3v3 on the shield - this removes parasitic voltage from 3v3 rail when MOSFET was turn off.
    * Moves power destination of "Power Jumper" section from "VIN" to the "5V" rail of R3/R4
    * Updates silk
    * Changes any "alt_rx/tx" net names to be "drx/dtx"
2023-10-13 Fixes power net names and mirrors translation mosfets
    * Changes 3v3_SW to 3v3_R3 to be more clear about the actual power source
    * Changes VCC to VUSB to also be more clear as to the source
    * Mirrors the source and drain on all translation mosfets so that that body diode is not biasing the 3v3 rail on the shield
2023-10-13 Moves USBC circuit up a smidgen in the schematic
2023-10-13 Minor changes to schematic elements
2023-10-13 Updates schematic elements again , Adds USB-C to silk
2023-10-13 Adds new production file for v12
2023-10-13 Removes old prototypes
2023-10-16 Removes v11, adds v12 production panel
2023-12-12 Periodic Update
2023-12-12 Build fix?
2023-12-12 Build failures
    Build failures
2023-12-12 Adding back gitcommit
2023-12-15 Updating latest
2023-12-22 Major hardware overview update
2024-01-02 Updating UART Select Switch description
2024-01-03 Updating Hardware overview and assembly
2024-01-05 Updates to naming per Digi
2024-01-05 Updating trademark naming
2024-01-05 Fixing hard copy links
2024-01-08 Updating per Eli notes
2024-01-08 Deployed 522f356 with MkDocs version: 1.5.3
